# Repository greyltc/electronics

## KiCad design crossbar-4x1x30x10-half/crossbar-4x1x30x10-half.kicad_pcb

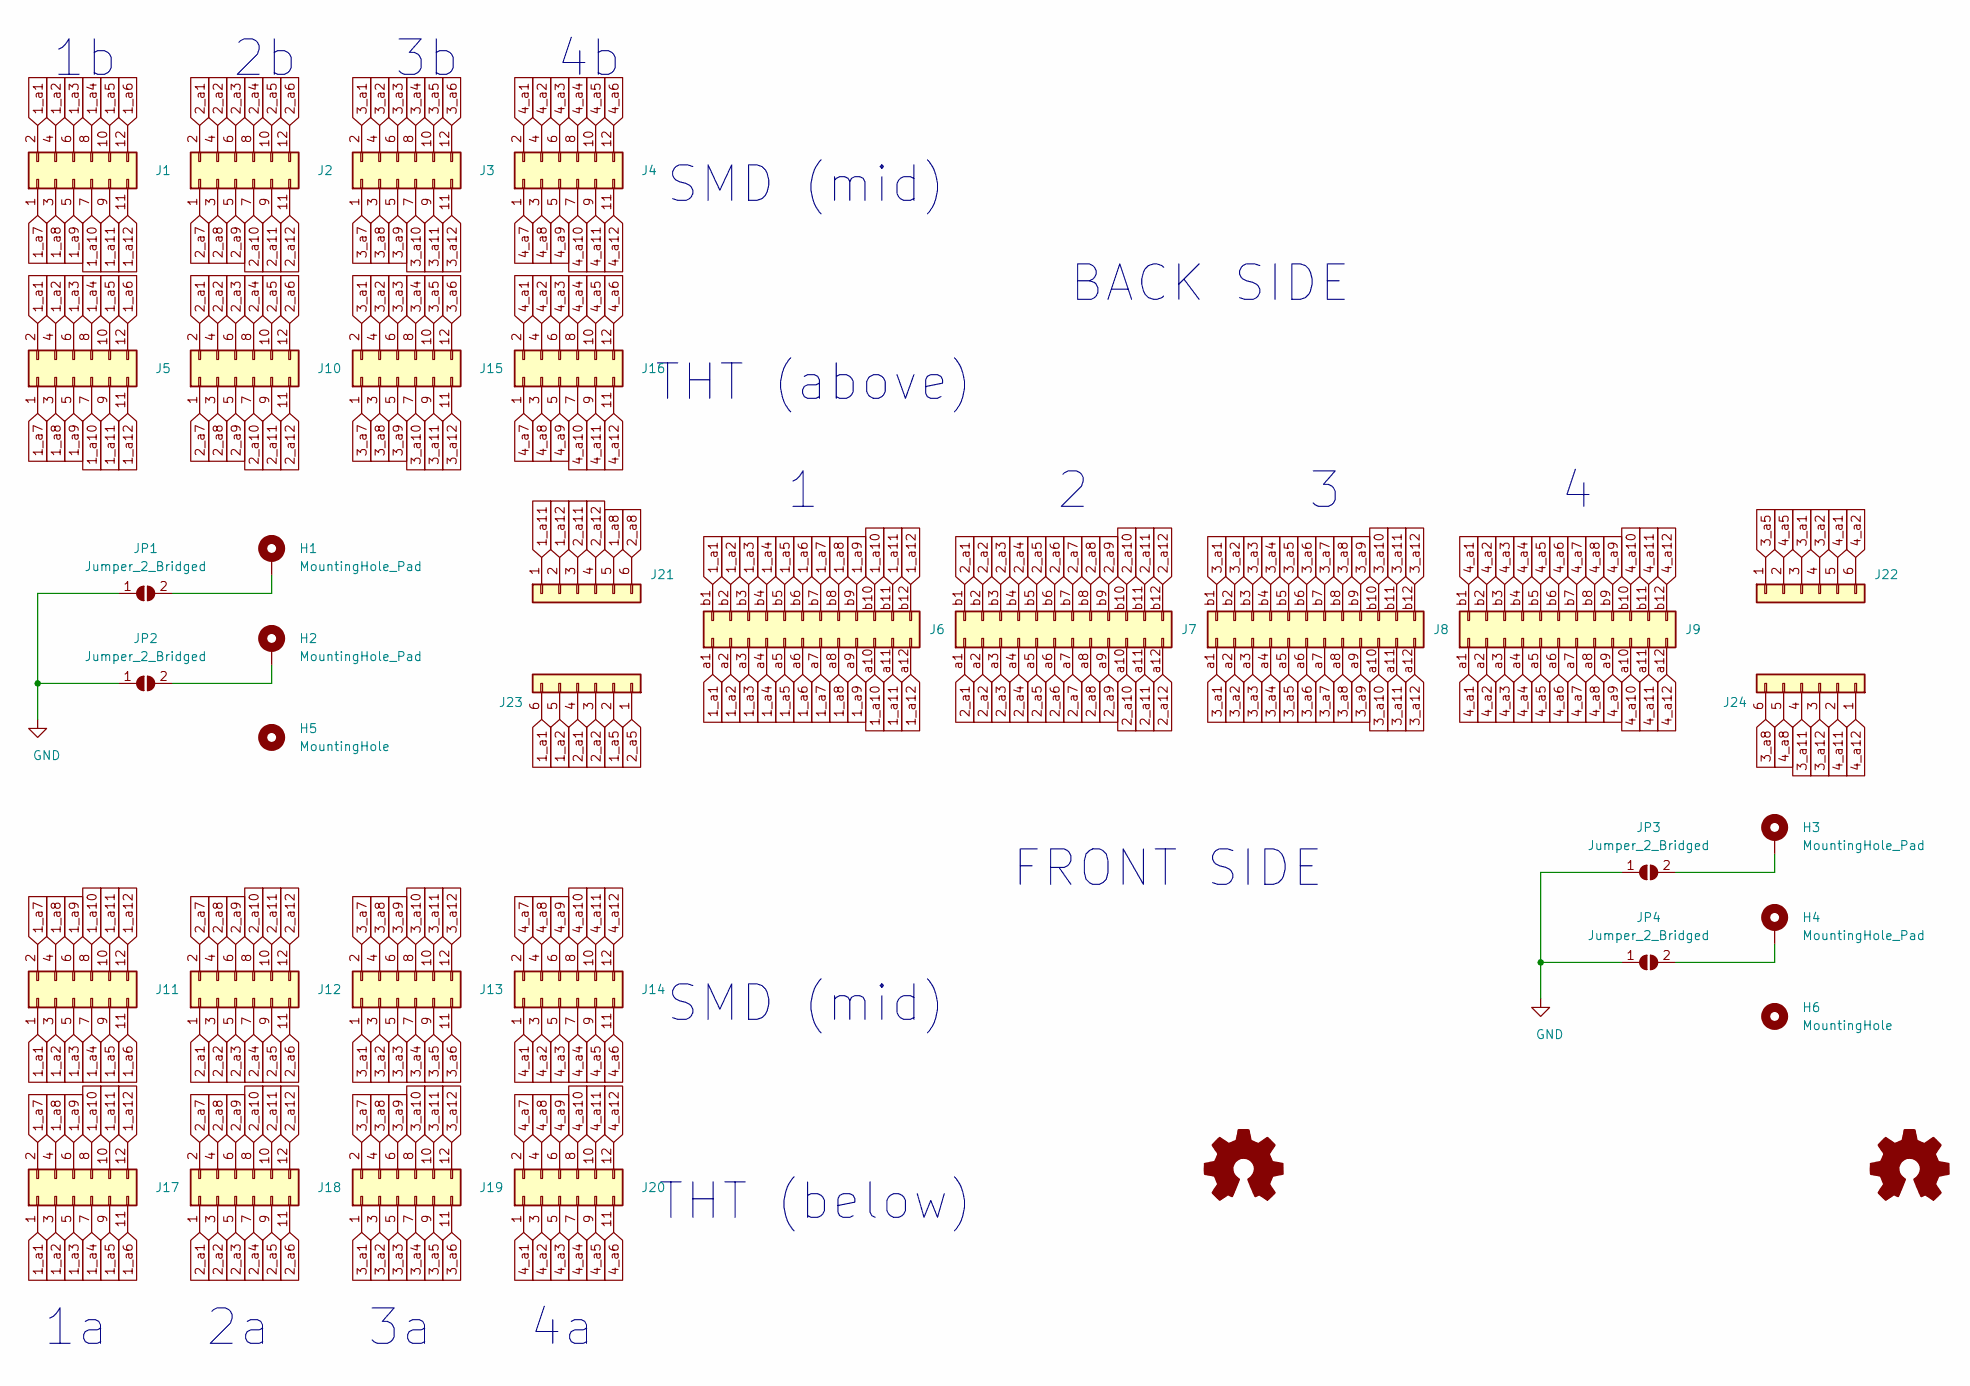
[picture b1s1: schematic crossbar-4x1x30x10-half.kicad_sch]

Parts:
H1, H2, H3, H4: MountingHole_Pad; MountingHole_2.2mm_M2_Pad_Via
H5, H6: MountingHole; MountingHole_3mm
J1, J2, J3, J4, J11, J12, J13, J14: Conn_02x06_Counter_Clockwise; 71609
J5, J10, J15, J16, J17, J18, J19, J20: Conn_02x06_Counter_Clockwise; PinHeader_2x06_P2.54mm_Vertical
J6, J7, J8, J9: Conn_02x12_Row_Letter_First; TMM-112-01-STRADDLE
J21, J22, J23, J24: Conn_01x06; MMS-106-02-X-SH
JP1, JP2, JP3, JP4: Jumper_2_Bridged; SolderJumper-2_P1.3mm_Open_RoundedPad1.0x1.5mm
LOGO1, LOGO2: Logo; logo_small

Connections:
1_a1: J1.2, J5.2, J6.a1, J6.b1, J11.1, J17.1, J23.6
1_a2: J1.4, J5.4, J6.a2, J6.b2, J11.3, J17.3, J23.5
1_a3: J1.6, J5.6, J6.a3, J6.b3, J11.5, J17.5
1_a4: J1.8, J5.8, J6.a4, J6.b4, J11.7, J17.7
1_a5: J1.10, J5.10, J6.a5, J6.b5, J11.9, J17.9, J23.2
1_a6: J1.12, J5.12, J6.a6, J6.b6, J11.11, J17.11
1_a7: J1.1, J5.1, J6.a7, J6.b7, J11.2, J17.2
1_a8: J1.3, J5.3, J6.a8, J6.b8, J11.4, J17.4, J21.5
1_a9: J1.5, J5.5, J6.a9, J6.b9, J11.6, J17.6
1_a10: J1.7, J5.7, J6.a10, J6.b10, J11.8, J17.8
1_a11: J1.9, J5.9, J6.a11, J6.b11, J11.10, J17.10, J21.1
1_a12: J1.11, J5.11, J6.a12, J6.b12, J11.12, J17.12, J21.2
2_a1: J2.2, J7.a1, J7.b1, J10.2, J12.1, J18.1, J23.4
2_a2: J2.4, J7.a2, J7.b2, J10.4, J12.3, J18.3, J23.3
2_a3: J2.6, J7.a3, J7.b3, J10.6, J12.5, J18.5
2_a4: J2.8, J7.a4, J7.b4, J10.8, J12.7, J18.7
2_a5: J2.10, J7.a5, J7.b5, J10.10, J12.9, J18.9, J23.1
2_a6: J2.12, J7.a6, J7.b6, J10.12, J12.11, J18.11
2_a7: J2.1, J7.a7, J7.b7, J10.1, J12.2, J18.2
2_a8: J2.3, J7.a8, J7.b8, J10.3, J12.4, J18.4, J21.6
2_a9: J2.5, J7.a9, J7.b9, J10.5, J12.6, J18.6
2_a10: J2.7, J7.a10, J7.b10, J10.7, J12.8, J18.8
2_a11: J2.9, J7.a11, J7.b11, J10.9, J12.10, J18.10, J21.3
2_a12: J2.11, J7.a12, J7.b12, J10.11, J12.12, J18.12, J21.4
3_a1: J3.2, J8.a1, J8.b1, J13.1, J15.2, J19.1, J22.3
3_a2: J3.4, J8.a2, J8.b2, J13.3, J15.4, J19.3, J22.4
3_a3: J3.6, J8.a3, J8.b3, J13.5, J15.6, J19.5
3_a4: J3.8, J8.a4, J8.b4, J13.7, J15.8, J19.7
3_a5: J3.10, J8.a5, J8.b5, J13.9, J15.10, J19.9, J22.1
3_a6: J3.12, J8.a6, J8.b6, J13.11, J15.12, J19.11
3_a7: J3.1, J8.a7, J8.b7, J13.2, J15.1, J19.2
3_a8: J3.3, J8.a8, J8.b8, J13.4, J15.3, J19.4, J24.6
3_a9: J3.5, J8.a9, J8.b9, J13.6, J15.5, J19.6
3_a10: J3.7, J8.a10, J8.b10, J13.8, J15.7, J19.8
3_a11: J3.9, J8.a11, J8.b11, J13.10, J15.9, J19.10, J24.4
3_a12: J3.11, J8.a12, J8.b12, J13.12, J15.11, J19.12, J24.3
4_a1: J4.2, J9.a1, J9.b1, J14.1, J16.2, J20.1, J22.5
4_a2: J4.4, J9.a2, J9.b2, J14.3, J16.4, J20.3, J22.6
4_a3: J4.6, J9.a3, J9.b3, J14.5, J16.6, J20.5
4_a4: J4.8, J9.a4, J9.b4, J14.7, J16.8, J20.7
4_a5: J4.10, J9.a5, J9.b5, J14.9, J16.10, J20.9, J22.2
4_a6: J4.12, J9.a6, J9.b6, J14.11, J16.12, J20.11
4_a7: J4.1, J9.a7, J9.b7, J14.2, J16.1, J20.2
4_a8: J4.3, J9.a8, J9.b8, J14.4, J16.3, J20.4, J24.5
4_a9: J4.5, J9.a9, J9.b9, J14.6, J16.5, J20.6
4_a10: J4.7, J9.a10, J9.b10, J14.8, J16.7, J20.8
4_a11: J4.9, J9.a11, J9.b11, J14.10, J16.9, J20.10, J24.2
4_a12: J4.11, J9.a12, J9.b12, J14.12, J16.11, J20.12, J24.1
GND: JP1.1 (A), JP2.1 (A), JP3.1 (A), JP4.1 (A)
unnamed: H1.1, JP1.2 (B)
unnamed: H2.1, JP2.2 (B)
unnamed: H3.1, JP3.2 (B)
unnamed: H4.1, JP4.2 (B)

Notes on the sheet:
SMD (mid)
THT (above)
THT (below)
FRONT SIDE
BACK SIDE

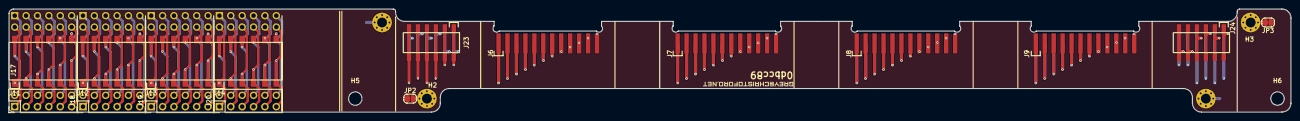
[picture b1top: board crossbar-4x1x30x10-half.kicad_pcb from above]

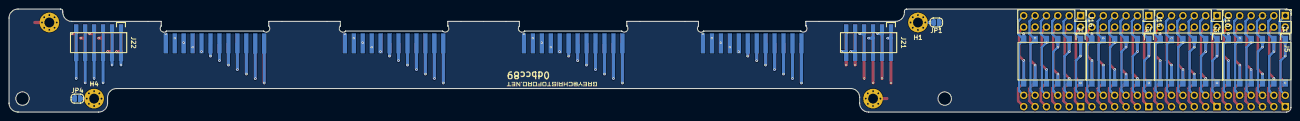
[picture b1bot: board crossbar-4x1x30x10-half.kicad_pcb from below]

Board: 6 copper layers, 286.3 x 23.0 mm, 36 parts (15 on the bottom side), 53 nets.

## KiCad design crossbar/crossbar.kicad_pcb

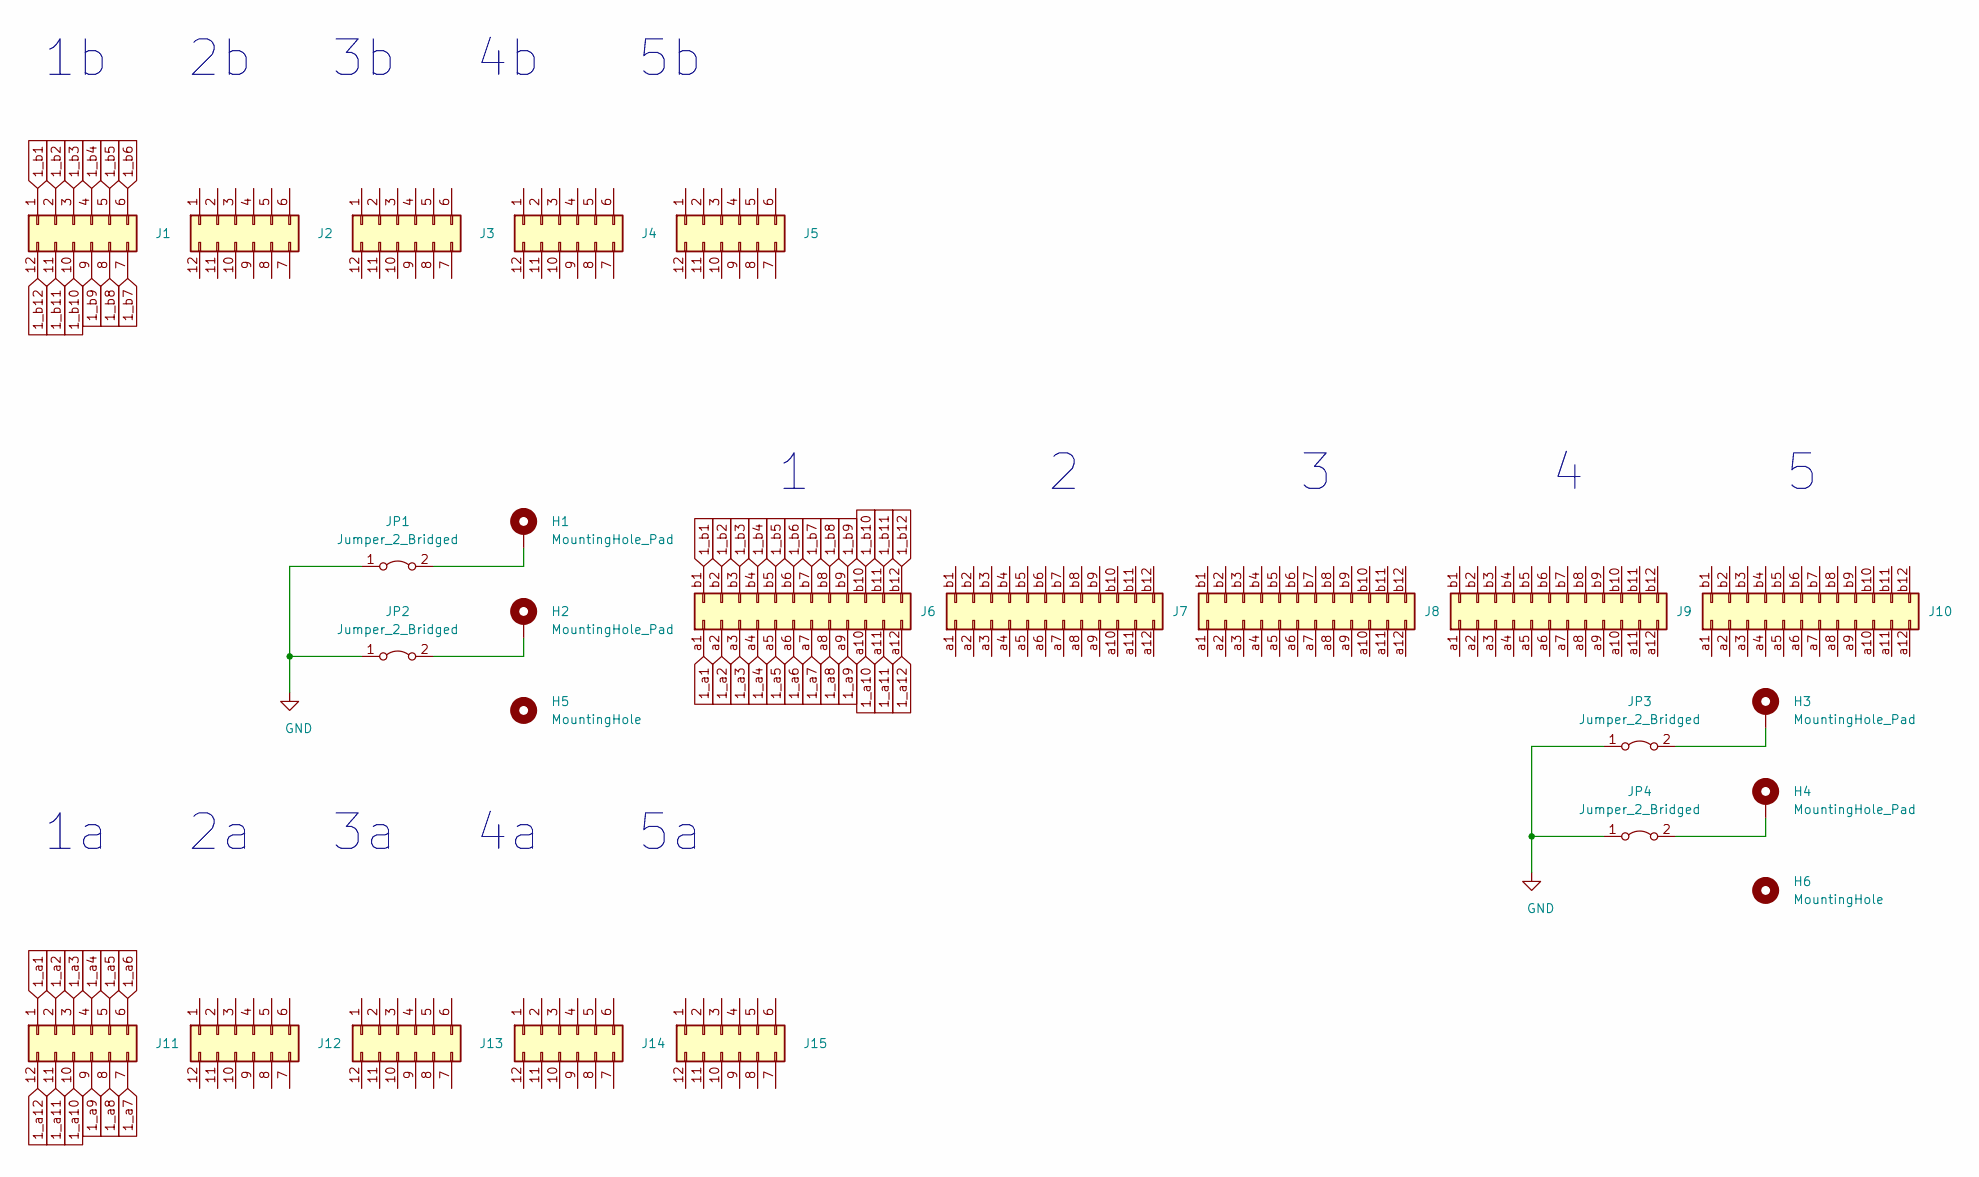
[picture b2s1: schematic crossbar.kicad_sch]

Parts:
H1, H2, H3, H4: MountingHole_Pad; MountingHole_2.2mm_M2_Pad_Via
H5, H6: MountingHole; MountingHole_3mm
J1, J2, J3, J4, J5, J11, J12, J13, J14, J15: Conn_02x06_Counter_Clockwise; 71609
J6, J7, J8, J9, J10: Conn_02x12_Row_Letter_First; TMM-112-01-STRADDLE
JP1, JP2, JP3, JP4: Jumper_2_Bridged; SolderJumper-2_P1.3mm_Bridged_RoundedPad1.0x1.5mm

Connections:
1_a1: J6.a1, J11.1
1_a2: J6.a2, J11.2
1_a3: J6.a3, J11.3
1_a4: J6.a4, J11.4
1_a5: J6.a5, J11.5
1_a6: J6.a6, J11.6
1_a7: J6.a7, J11.7
1_a8: J6.a8, J11.8
1_a9: J6.a9, J11.9
1_a10: J6.a10, J11.10
1_a11: J6.a11, J11.11
1_a12: J6.a12, J11.12
1_b1: J1.1, J6.b1
1_b2: J1.2, J6.b2
1_b3: J1.3, J6.b3
1_b4: J1.4, J6.b4
1_b5: J1.5, J6.b5
1_b6: J1.6, J6.b6
1_b7: J1.7, J6.b7
1_b8: J1.8, J6.b8
1_b9: J1.9, J6.b9
1_b10: J1.10, J6.b10
1_b11: J1.11, J6.b11
1_b12: J1.12, J6.b12
GND: JP1.1 (A), JP2.1 (A), JP3.1 (A), JP4.1 (A)
unnamed: H1.1, JP1.2 (B)
unnamed: H2.1, JP2.2 (B)
unnamed: H3.1, JP3.2 (B)
unnamed: H4.1, JP4.2 (B)

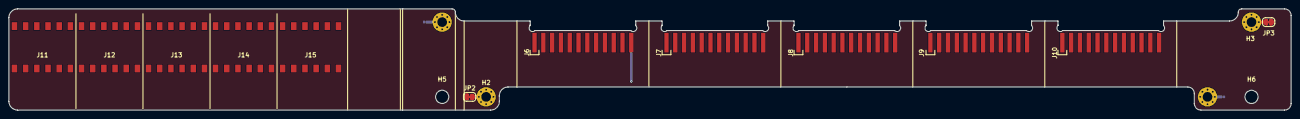
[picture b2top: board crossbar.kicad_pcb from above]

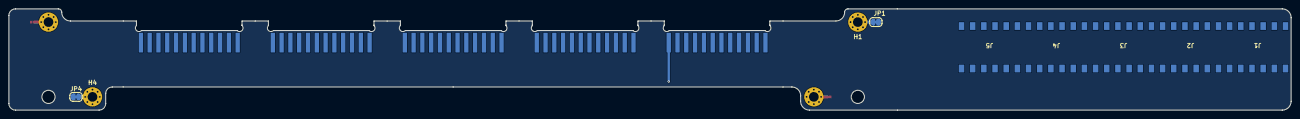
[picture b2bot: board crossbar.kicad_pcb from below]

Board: 12 copper layers, 291.5 x 23.0 mm, 25 parts (9 on the bottom side), 29 nets.

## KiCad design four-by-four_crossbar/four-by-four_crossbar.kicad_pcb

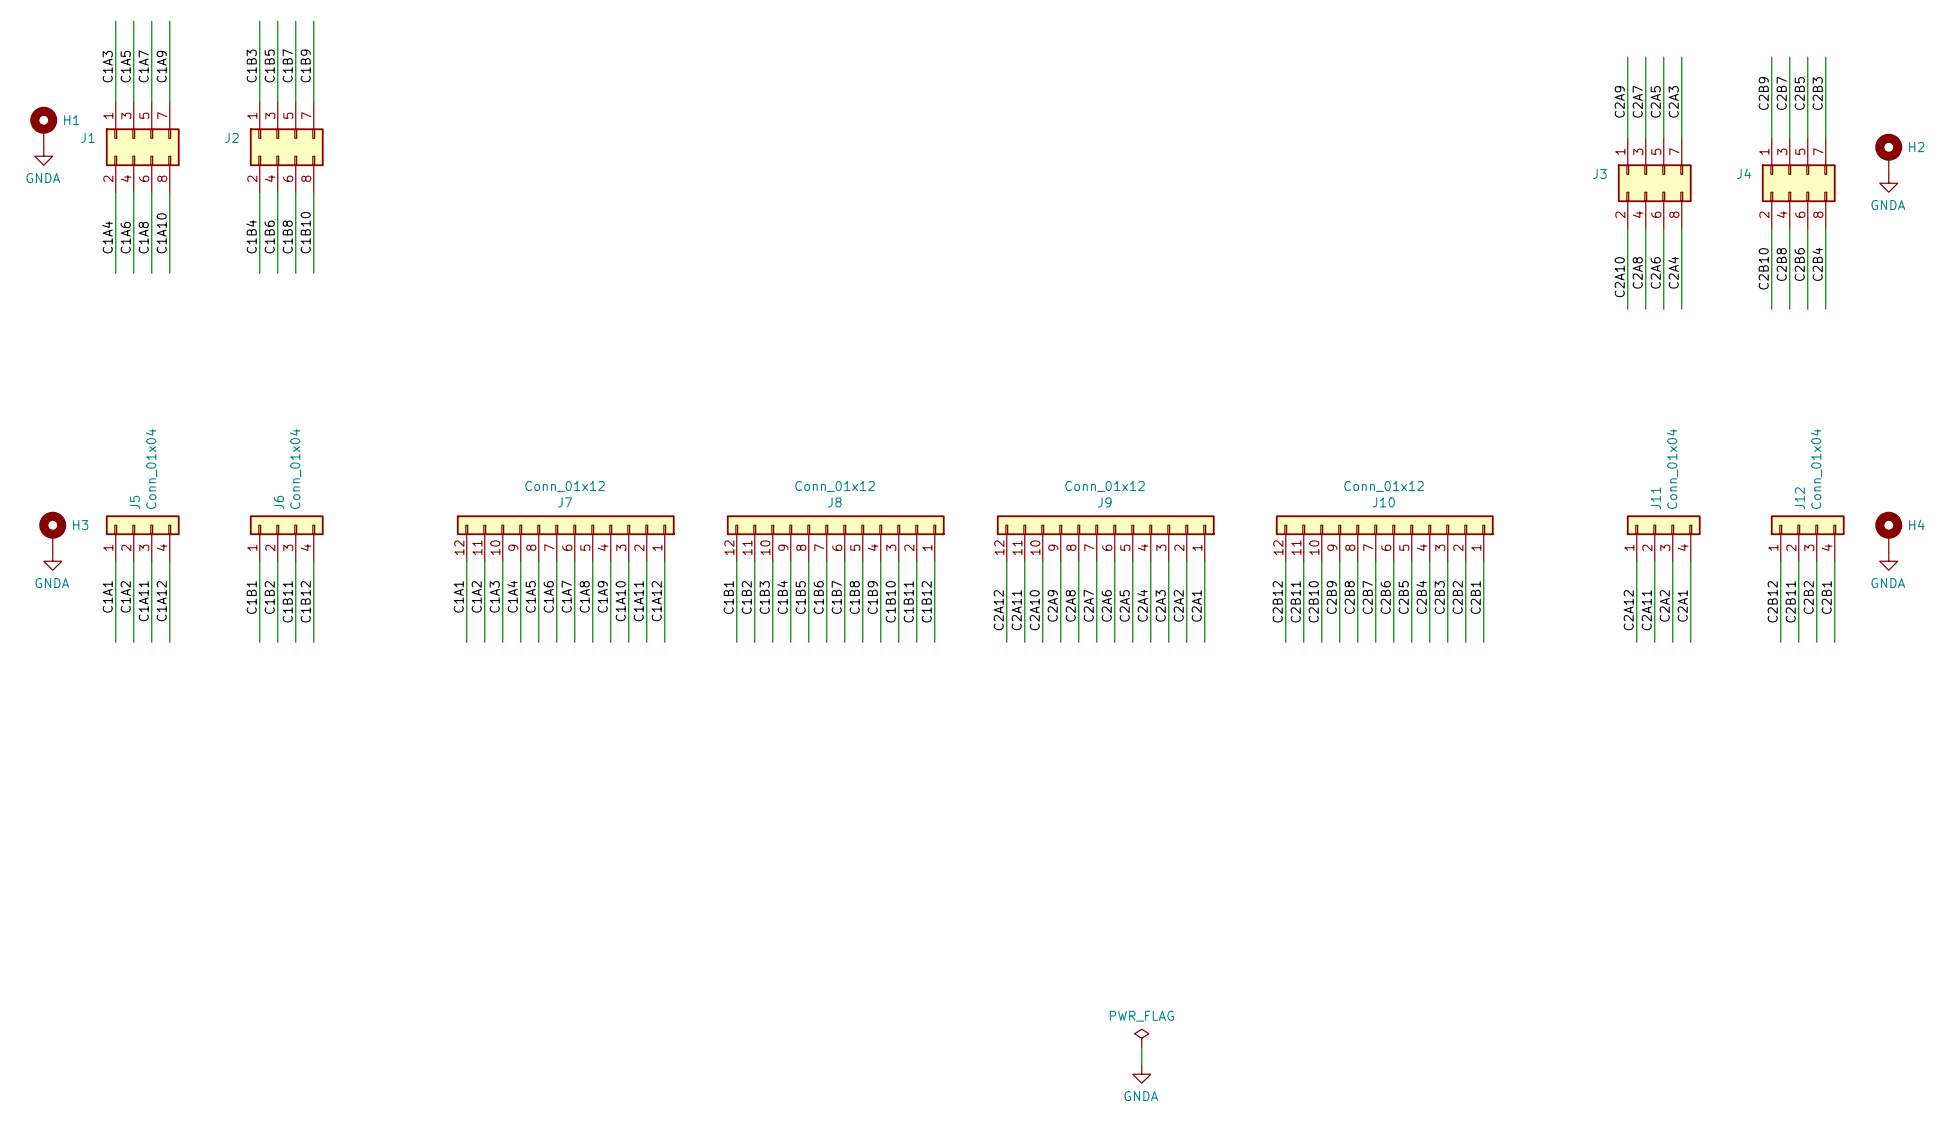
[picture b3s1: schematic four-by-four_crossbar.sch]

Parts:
H1, H2, H3, H4: MountingHole_Pad; MountingHole_2.2mm_M2_Pad
J1, J2, J3, J4: Conn_02x04_Odd_Even; PinSocket_2x04_P2.00mm_Vertical_SMD
J5, J6, J11, J12: Conn_01x04; PinSocket_1x04_P2.00mm_Vertical_SMD_Pin1Left
J7, J8, J9, J10: Conn_01x12; SAMTEC-MMS-112-02-X-SH-BRIDGE-PAD

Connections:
/C1A1: J5.1, J7.12
/C1A2: J5.2, J7.11
/C1A3: J1.1, J7.10
/C1A4: J1.2, J7.9
/C1A5: J1.3, J7.8
/C1A6: J1.4, J7.7
/C1A7: J1.5, J7.6
/C1A8: J1.6, J7.5
/C1A9: J1.7, J7.4
/C1A10: J1.8, J7.3
/C1A11: J5.3, J7.2
/C1A12: J5.4, J7.1
/C1B1: J6.1, J8.12
/C1B2: J6.2, J8.11
/C1B3: J2.1, J8.10
/C1B4: J2.2, J8.9
/C1B5: J2.3, J8.8
/C1B6: J2.4, J8.7
/C1B7: J2.5, J8.6
/C1B8: J2.6, J8.5
/C1B9: J2.7, J8.4
/C1B10: J2.8, J8.3
/C1B11: J6.3, J8.2
/C1B12: J6.4, J8.1
/C2A1: J9.1, J11.4
/C2A2: J9.2, J11.3
/C2A3: J3.7, J9.3
/C2A4: J3.8, J9.4
/C2A5: J3.5, J9.5
/C2A6: J3.6, J9.6
/C2A7: J3.3, J9.7
/C2A8: J3.4, J9.8
/C2A9: J3.1, J9.9
/C2A10: J3.2, J9.10
/C2A11: J9.11, J11.2
/C2A12: J9.12, J11.1
/C2B1: J10.1, J12.4
/C2B2: J10.2, J12.3
/C2B3: J4.7, J10.3
/C2B4: J4.8, J10.4
/C2B5: J4.5, J10.5
/C2B6: J4.6, J10.6
/C2B7: J4.3, J10.7
/C2B8: J4.4, J10.8
/C2B9: J4.1, J10.9
/C2B10: J4.2, J10.10
/C2B11: J10.11, J12.2
/C2B12: J10.12, J12.1
GNDA: H1.1, H2.1, H3.1, H4.1

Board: 4 copper layers, 16 parts (4 on the bottom side), 49 nets, no tracks yet.

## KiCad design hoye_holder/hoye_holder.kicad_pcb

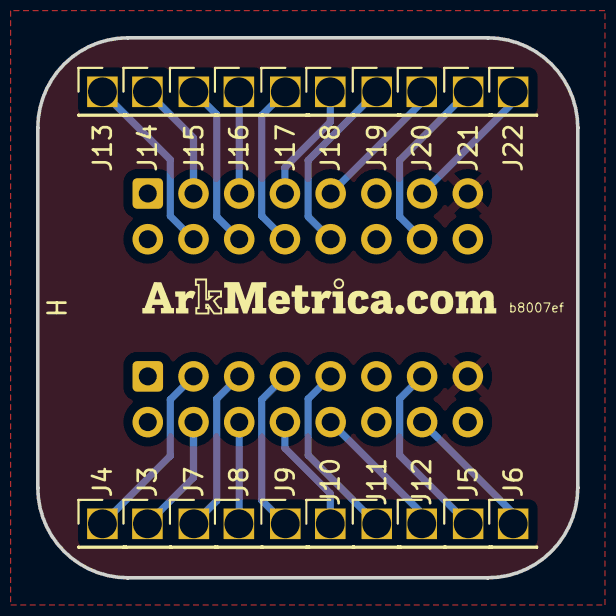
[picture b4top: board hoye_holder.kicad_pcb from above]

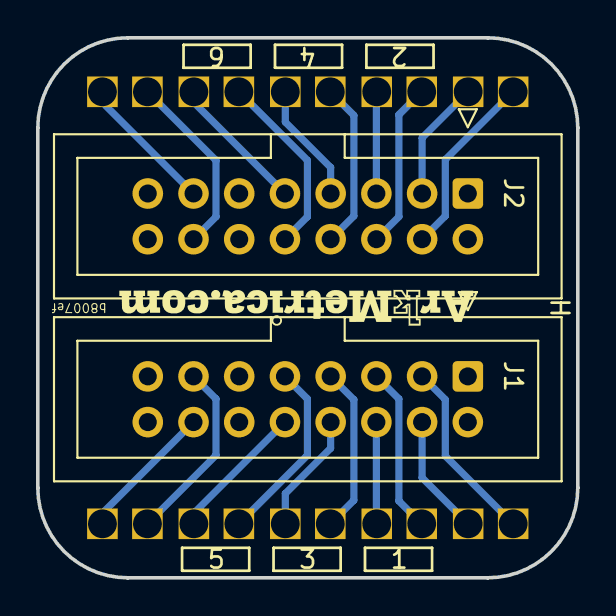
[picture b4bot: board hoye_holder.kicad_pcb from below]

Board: 2 copper layers, 30.0 x 30.0 mm, 24 parts (3 on the bottom side), 21 nets.

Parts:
J1, J2: Conn_02x08_Odd_Even; HIF3FC-16PA-2.54DSA(71)
J3, J4, J5, J6, J7, J8, J9, J10, J11, J12, J13, J14, J15, J16, J17, J18, J19, J20, J21, J22: Conn_01x01; S25-022+P25-4023_OFF
SYM1, SYM2: Logo_Open_Hardware_Small; site_small

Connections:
/I_1: J1.5, J7.1
/I_2: J2.5, J16.1
/I_3: J1.7, J9.1
/I_4: J2.7, J18.1
/I_5: J1.9, J11.1
/I_6: J2.9, J20.1
/I_EV_B: J2.13, J22.1
/I_EV_T: J2.3, J14.1
/I_OD_B: J1.13, J5.1
/I_OD_T: J1.3, J4.1
/V_1: J1.6, J8.1
/V_2: J2.6, J15.1
/V_3: J1.8, J10.1
/V_4: J2.8, J17.1
/V_5: J1.10, J12.1
/V_6: J2.10, J19.1
/V_EV_B: J2.14, J21.1
/V_EV_T: J2.4, J13.1
/V_OD_B: J1.14, J6.1
/V_OD_T: J1.4, J3.1
GND: J1.15, J2.15

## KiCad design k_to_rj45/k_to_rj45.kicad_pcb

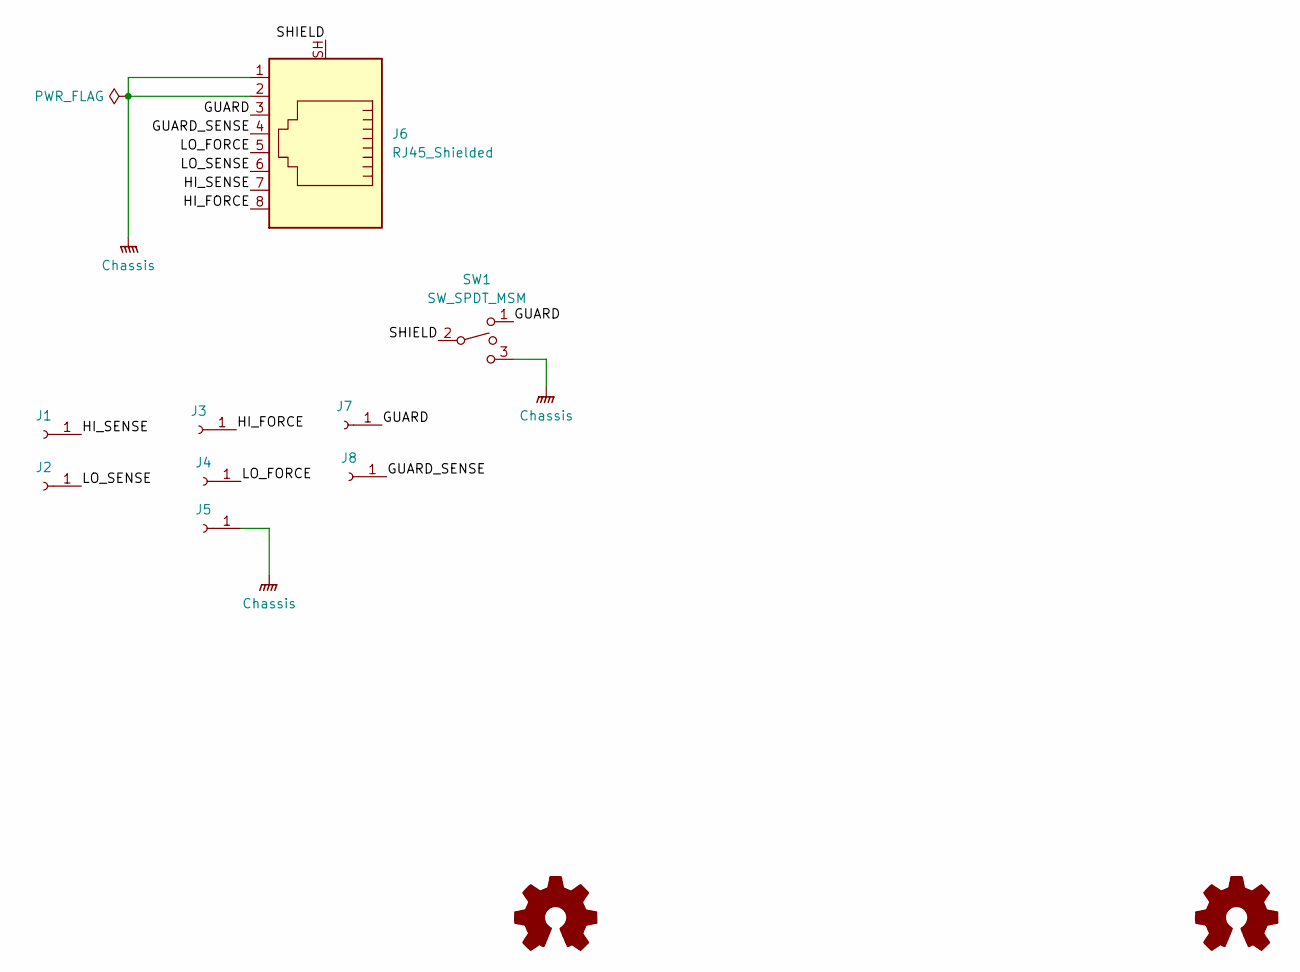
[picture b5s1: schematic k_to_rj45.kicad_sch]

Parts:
J1, J2, J3, J4, J5, J7, J8: Conn_01x01_Female; Mounting_Wuerth_WA-SMSI-4.5mm_H3mm_9774030482_pad_mod
J6: RJ45_Shielded; RJ45_TE_100616
LOGO1, LOGO2: Logo_Open_Hardware_Small; logo
SW1: SW_SPDT_MSM; SPDT_slide_switch; mfg part 1103M2S3CQE2

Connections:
/GUARD: J6.3, J7.1, SW1.1
/GUARD_SENSE: J6.4, J8.1
/HI_FORCE: J3.1, J6.8
/HI_SENSE: J1.1, J6.7
/LO_FORCE: J4.1, J6.5
/LO_SENSE: J2.1, J6.6
/SHIELD: J6.SH, SW1.2
GNDPWR: J5.1, J6.1, J6.2, SW1.3

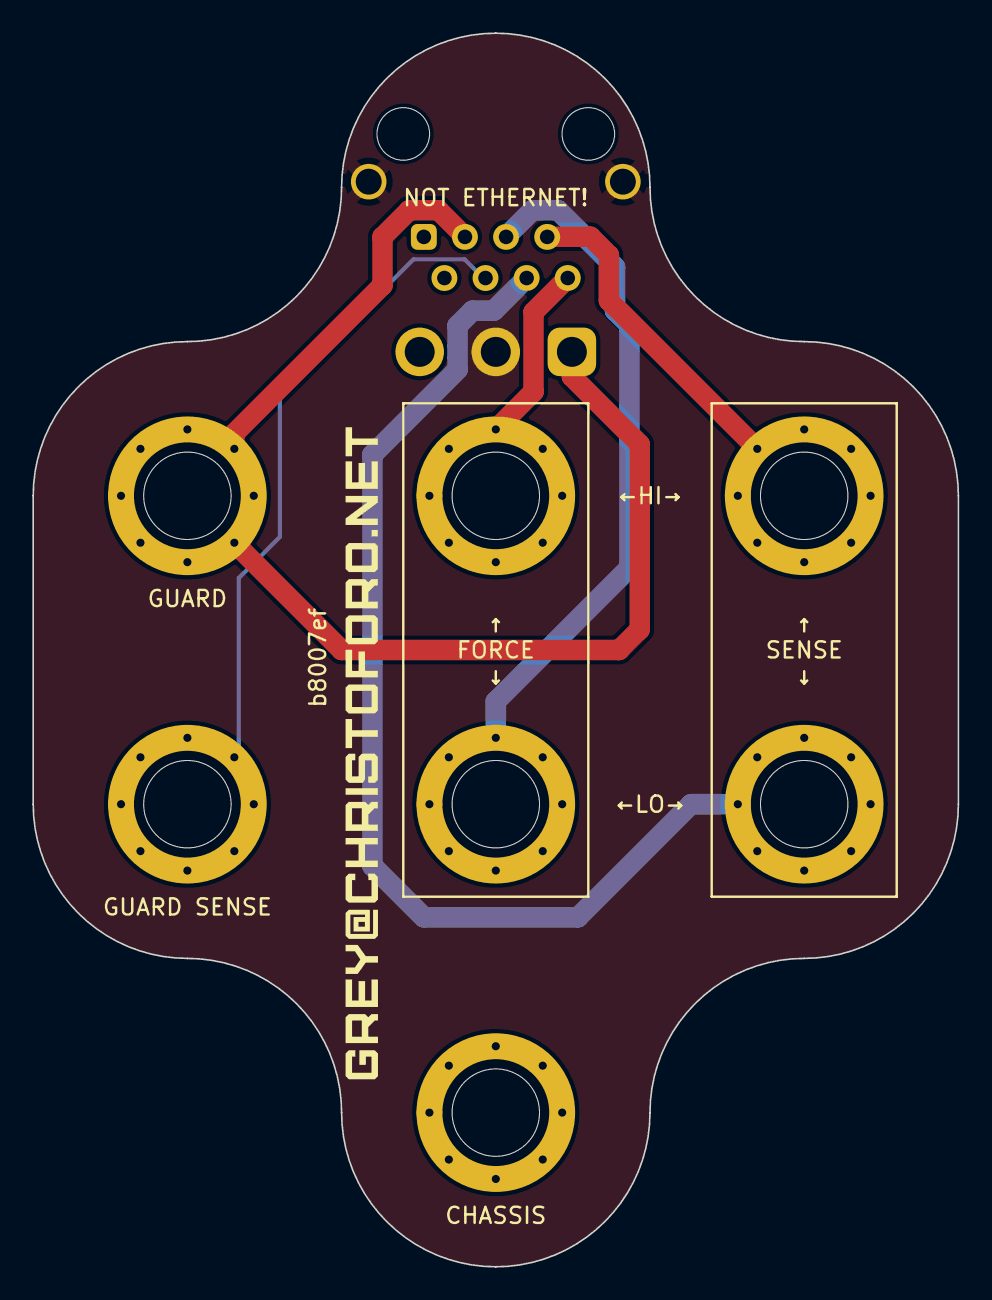
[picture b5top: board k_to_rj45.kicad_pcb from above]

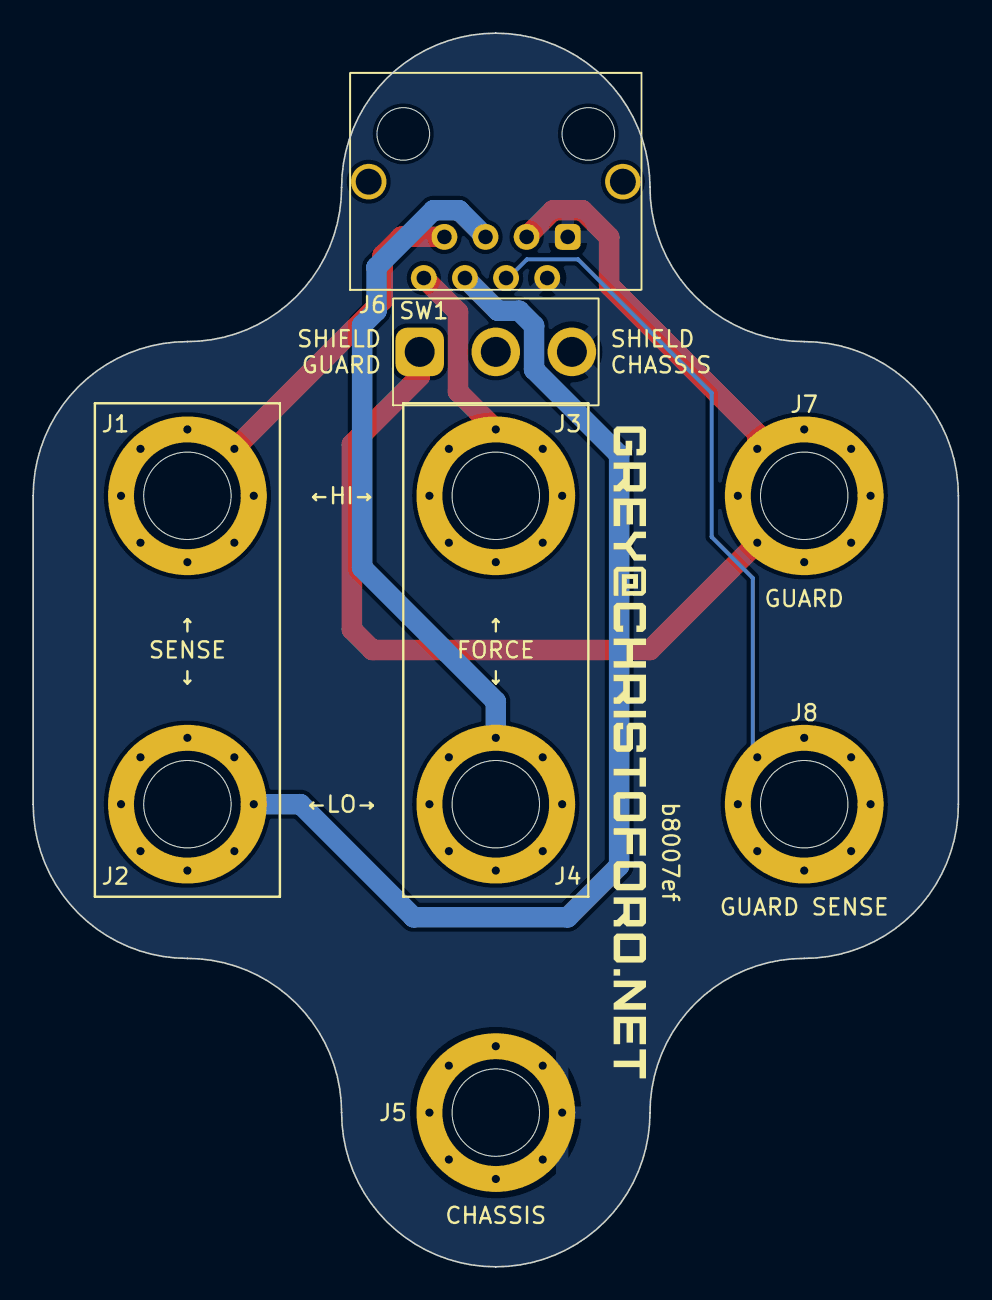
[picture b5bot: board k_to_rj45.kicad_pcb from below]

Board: 2 copper layers, 57.2 x 76.2 mm, 11 parts (10 on the bottom side), 8 nets.

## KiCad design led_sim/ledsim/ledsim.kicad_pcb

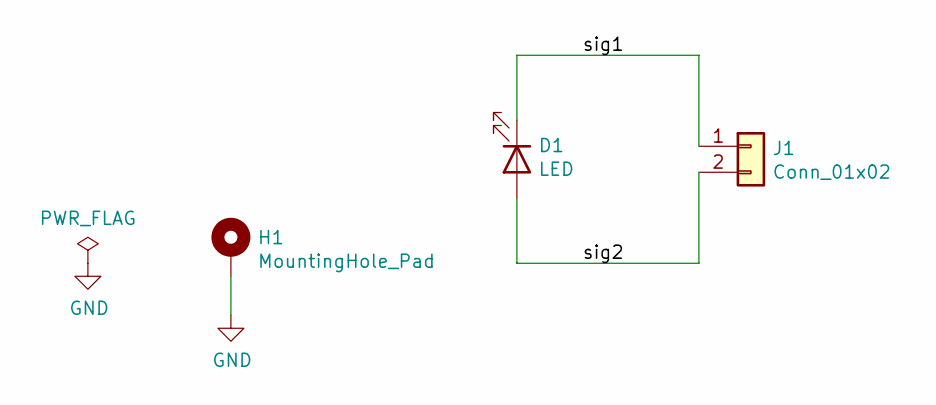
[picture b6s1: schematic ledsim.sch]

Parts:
D1: LED; LED_2010_5025Metric
H1: MountingHole_Pad; MountingHole_2.2mm_M2_Pad
J1: Conn_01x02; PinHeader_1x02_P2.00mm_Vertical

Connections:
/sig1: D1.1 (K), J1.1
/sig2: D1.2 (A), J1.2
GND: H1.1

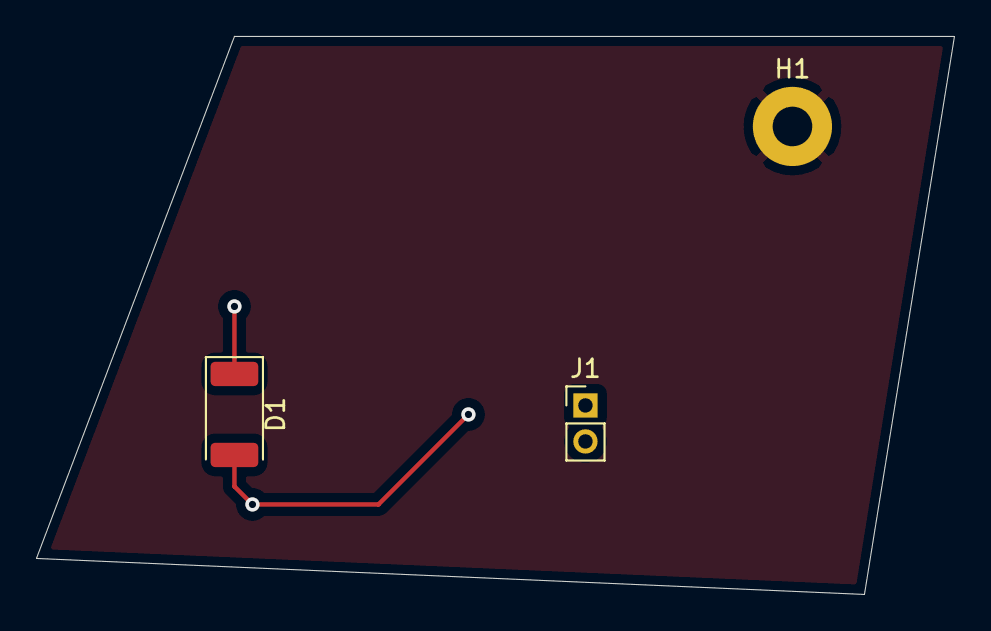
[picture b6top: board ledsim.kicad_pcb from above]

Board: 4 copper layers, 51.0 x 31.0 mm, 3 parts (0 on the bottom side), 2 nets.
